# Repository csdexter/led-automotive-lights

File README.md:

#LED replacements for automotive light fixtures#

(C) 2013 Radu - Eosif Mihailescu <radu.mihailescu@linux360.ro>

All files in this repository are licensed under the
**GNU Generic Public License v3**, a copy of whose text can be accessed
 [here](http://www.gnu.org/licenses/gpl.html).

This repository contains [EDA](http://en.wikipedia.org/wiki/Electronic_design_automation) source files and associated software sources/configuration data for various LED-based replacements for common automotive light fixtures. The EDA files are in CadSoft Eagle 6 format. Only the `.SCH` (schematic) and `.BRD` (board) files are provided as all data needed for manufacturing can easily be derived from the former. No guarantee is made as to which minor version of Eagle was used to save the file, but it *may* be the latest at the time of this writing.

The board description files *may* contain routing information or be supplied unrouted. In the former case, the routing artwork *may* have been generated by either Eagle's internal autorouter or [FreeRouting](http://www.freerouting.net/).

All files included here are compatible with the free version of Eagle (i.e. describe PCBs having no more than 2 layers and measuring no more than 10cm by 8cm each).

Git tags will be used to mark specific revisions that were actually manufactured so that a correspondence between the evolution of the sources and the status of physical by-products can be maintained.

##WARNING##
*Unless and until explictily noted otherwise, the engineering materials here are laboratory quality and neither intended for manufacturing in production quantities nor for distribution (e.g. as kits) to end-users. The design data here does not explicitly follow any widely-accepted safety/security/EMI regulation or standard, therefore any manufacturing and/or usage in connection with live equipment is entirely at your own risk. Furthermore, the products described by the engineering materials here have not been subjected to any kind of type approval, including for use on a motor vehicle operating on public roads.*

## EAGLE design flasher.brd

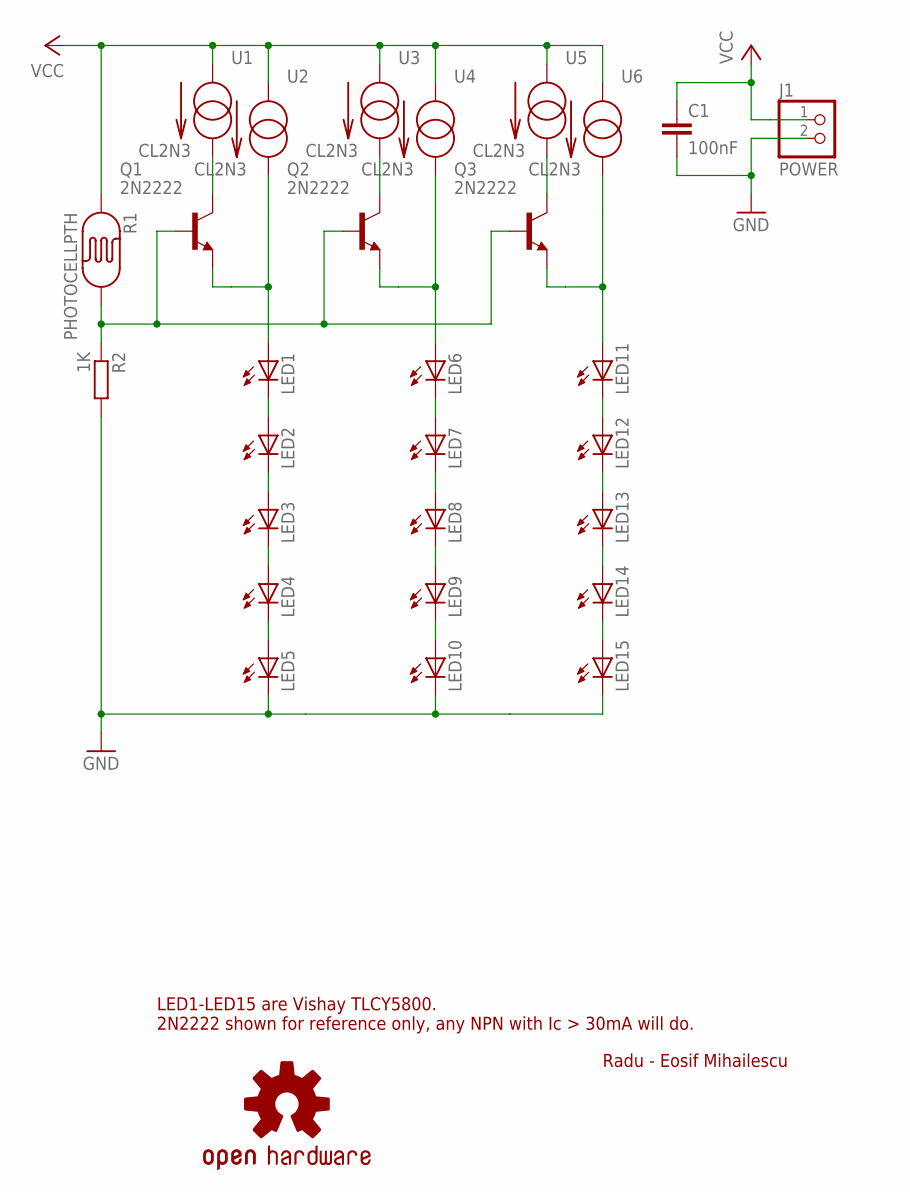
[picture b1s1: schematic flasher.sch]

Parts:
C1: 100nF; C050-025X075
J1: POWER; 1X02/90
LED1, LED2, LED3, LED4, LED5, LED6, LED7, LED8, LED9, LED10, LED11, LED12, LED13, LED14, LED15: LED5MM
LOGO1: OSHW-LOGOL; OSHW-LOGO-L
Q1, Q2, Q3: 2N2222; TO92-EBC
R1: PHOTOCELLPTH; PHOTOCELL
R2: 1K; 0204/7
U1, U2, U3, U4, U5, U6: CL2N3; TO-92

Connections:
GND: C1.2, J1.2, LED5.K (C), LED10.K (C), LED15.K (C), R2.2
unnamed: LED1.K (C), LED2.A
unnamed: LED2.K (C), LED3.A
unnamed: LED3.K (C), LED4.A
unnamed: LED1.A, Q1.E, U2.3 (OUT)
unnamed: LED4.K (C), LED5.A
unnamed: Q1.C, U1.3 (OUT)
unnamed: Q2.C, U3.3 (OUT)
unnamed: LED6.K (C), LED7.A
unnamed: LED7.K (C), LED8.A
unnamed: LED8.K (C), LED9.A
unnamed: LED6.A, Q2.E, U4.3 (OUT)
unnamed: LED9.K (C), LED10.A
unnamed: Q3.C, U5.3 (OUT)
unnamed: LED11.K (C), LED12.A
unnamed: LED12.K (C), LED13.A
unnamed: LED13.K (C), LED14.A
unnamed: LED11.A, Q3.E, U6.3 (OUT)
unnamed: LED14.K (C), LED15.A
SENSE: Q1.B, Q2.B, Q3.B, R1.2, R2.1
VCC: C1.1, J1.1, R1.1, U1.1 (IN), U2.1 (IN), U3.1 (IN), U4.1 (IN), U5.1 (IN), U6.1 (IN)

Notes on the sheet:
Radu - Eosif Mihailescu
LED1-LED15 are Vishay TLCY5800. 2N2222 shown for reference only, any NPN with Ic > 30mA will do.

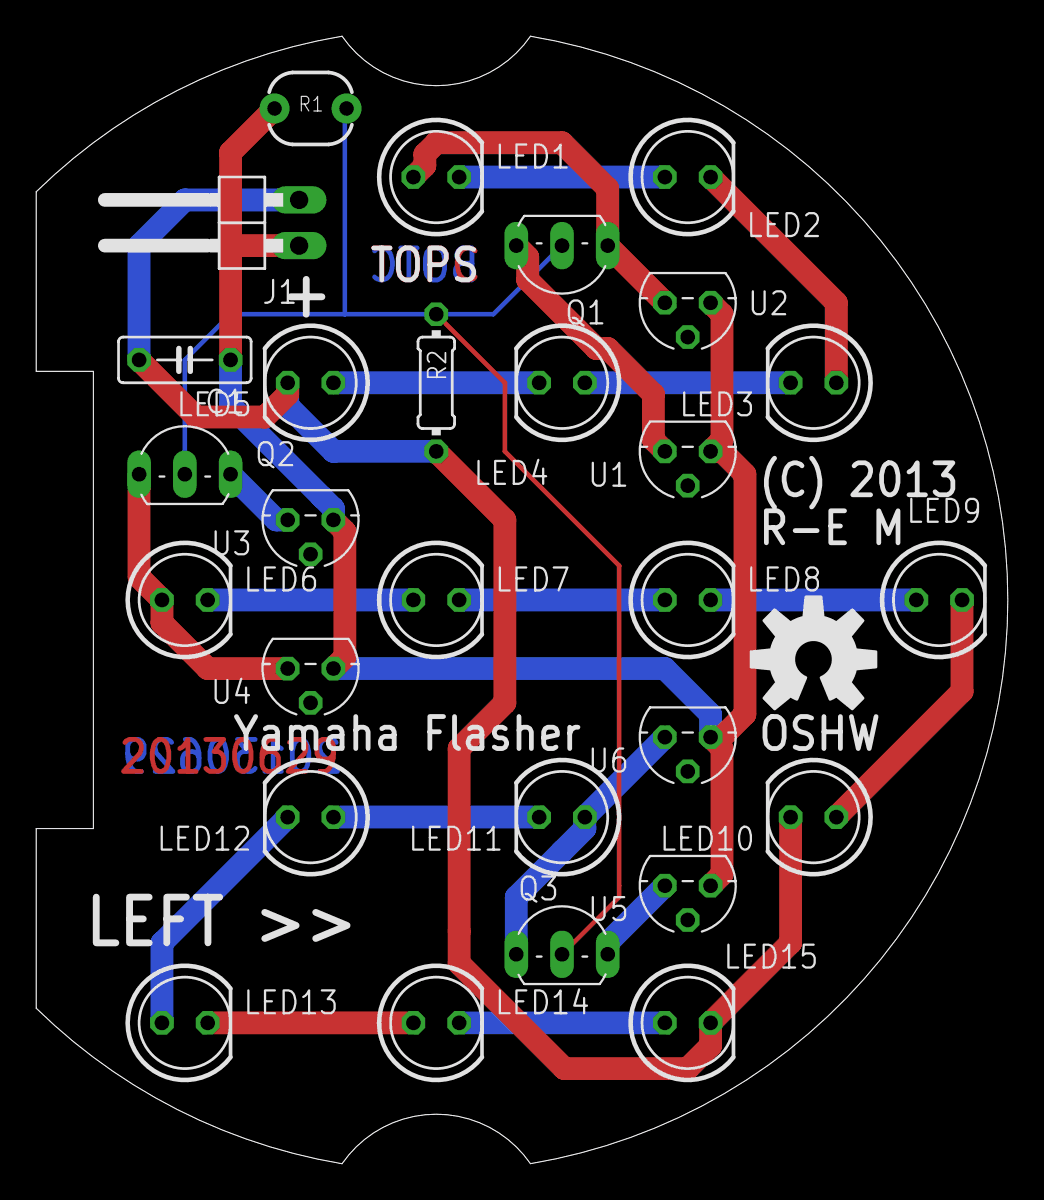
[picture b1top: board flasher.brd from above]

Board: 2 copper layers, 54.0 x 62.6 mm, 29 parts (0 on the bottom side), 21 nets.

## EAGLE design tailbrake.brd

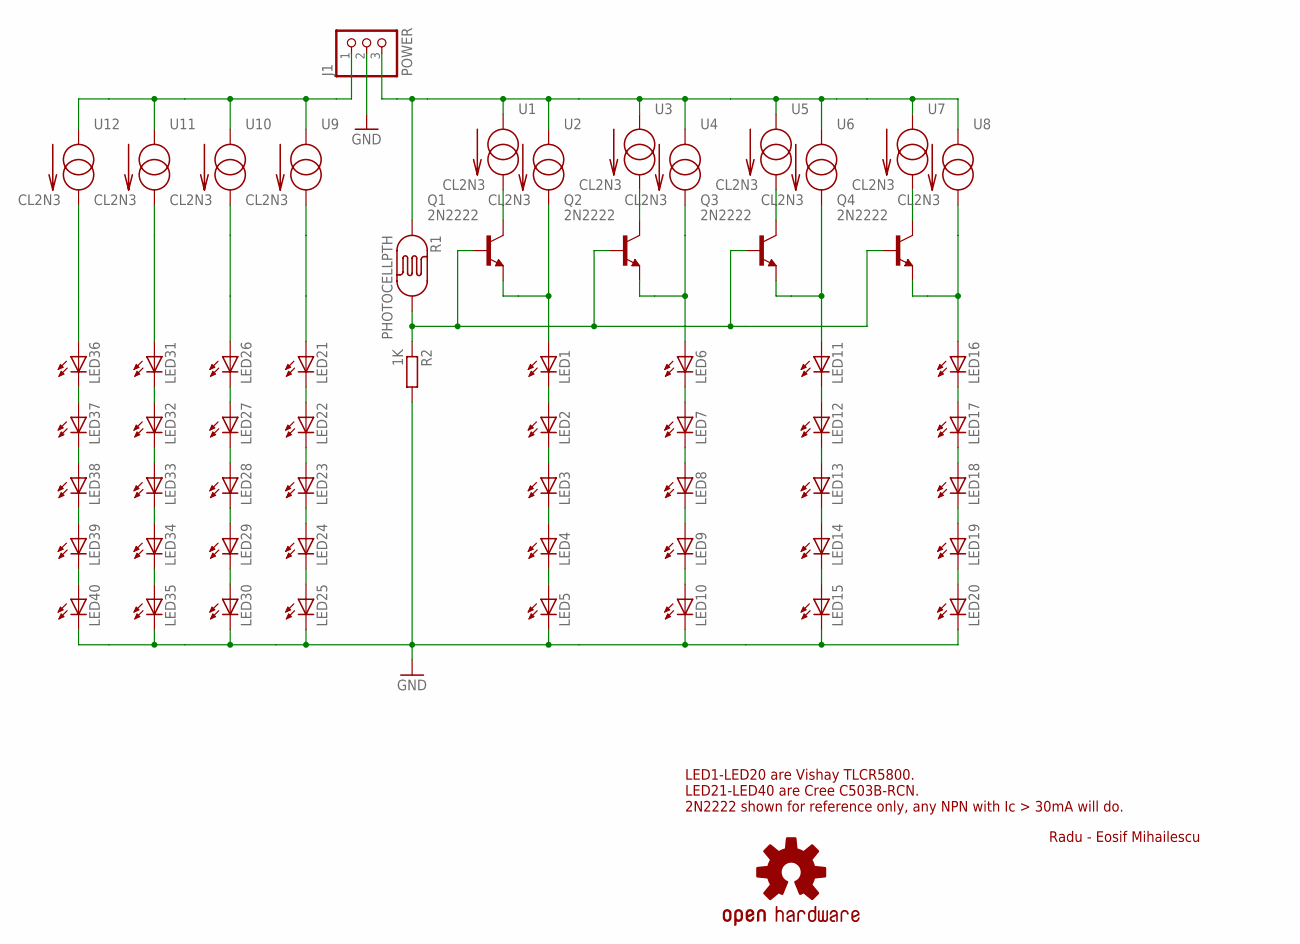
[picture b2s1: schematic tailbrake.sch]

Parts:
J1: POWER; 1X03/90
LED1, LED2, LED3, LED4, LED5, LED6, LED7, LED8, LED9, LED10, LED11, LED12, LED13, LED14, LED15, LED16, LED17, LED18, LED19, LED20, LED21, LED22, LED23, LED24, LED25, LED26, LED27, LED28, LED29, LED30, LED31, LED32, LED33, LED34, LED35, LED36, LED37, LED38, LED39, LED40: LED5MM
LOGO1: OSHW-LOGOL; OSHW-LOGO-L
Q1, Q2, Q3, Q4: 2N2222; TO92-EBC
R1: PHOTOCELLPTH; PHOTOCELL
R2: 1K; 0204/7
U1, U2, U3, U4, U5, U6, U7, U8, U9, U10, U11, U12: CL2N3; TO-92

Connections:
BRAKE: J1.3, R1.1, U1.1 (IN), U2.1 (IN), U3.1 (IN), U4.1 (IN), U5.1 (IN), U6.1 (IN), U7.1 (IN), U8.1 (IN)
GND: J1.2, LED5.K (C), LED10.K (C), LED15.K (C), LED20.K (C), LED25.K (C), LED30.K (C), LED35.K (C), LED40.K (C), R2.2
unnamed: LED1.K (C), LED2.A
unnamed: LED2.K (C), LED3.A
unnamed: LED3.K (C), LED4.A
unnamed: LED1.A, Q1.E, U2.3 (OUT)
unnamed: LED4.K (C), LED5.A
unnamed: Q1.C, U1.3 (OUT)
unnamed: Q2.C, U3.3 (OUT)
unnamed: LED6.K (C), LED7.A
unnamed: LED7.K (C), LED8.A
unnamed: LED8.K (C), LED9.A
unnamed: LED6.A, Q2.E, U4.3 (OUT)
unnamed: LED9.K (C), LED10.A
unnamed: Q3.C, U5.3 (OUT)
unnamed: LED11.K (C), LED12.A
unnamed: LED12.K (C), LED13.A
unnamed: LED13.K (C), LED14.A
unnamed: LED11.A, Q3.E, U6.3 (OUT)
unnamed: LED14.K (C), LED15.A
unnamed: LED16.K (C), LED17.A
unnamed: LED17.K (C), LED18.A
unnamed: LED18.K (C), LED19.A
unnamed: LED16.A, Q4.E, U8.3 (OUT)
unnamed: LED19.K (C), LED20.A
unnamed: Q4.C, U7.3 (OUT)
unnamed: LED21.K (C), LED22.A
unnamed: LED22.K (C), LED23.A
unnamed: LED23.K (C), LED24.A
unnamed: LED21.A, U9.3 (OUT)
unnamed: LED24.K (C), LED25.A
unnamed: LED26.K (C), LED27.A
unnamed: LED27.K (C), LED28.A
unnamed: LED28.K (C), LED29.A
unnamed: LED26.A, U10.3 (OUT)
unnamed: LED29.K (C), LED30.A
unnamed: LED31.K (C), LED32.A
unnamed: LED32.K (C), LED33.A
unnamed: LED33.K (C), LED34.A
unnamed: LED31.A, U11.3 (OUT)
unnamed: LED34.K (C), LED35.A
unnamed: LED36.K (C), LED37.A
unnamed: LED37.K (C), LED38.A
unnamed: LED38.K (C), LED39.A
unnamed: LED36.A, U12.3 (OUT)
unnamed: LED39.K (C), LED40.A
SENSE: Q1.B, Q2.B, Q3.B, Q4.B, R1.2, R2.1
TAIL: J1.1, U9.1 (IN), U10.1 (IN), U11.1 (IN), U12.1 (IN)

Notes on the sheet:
Radu - Eosif Mihailescu
LED1-LED20 are Vishay TLCR5800. LED21-LED40 are Cree C503B-RCN. 2N2222 shown for reference only, any NPN with Ic > 30mA will do.

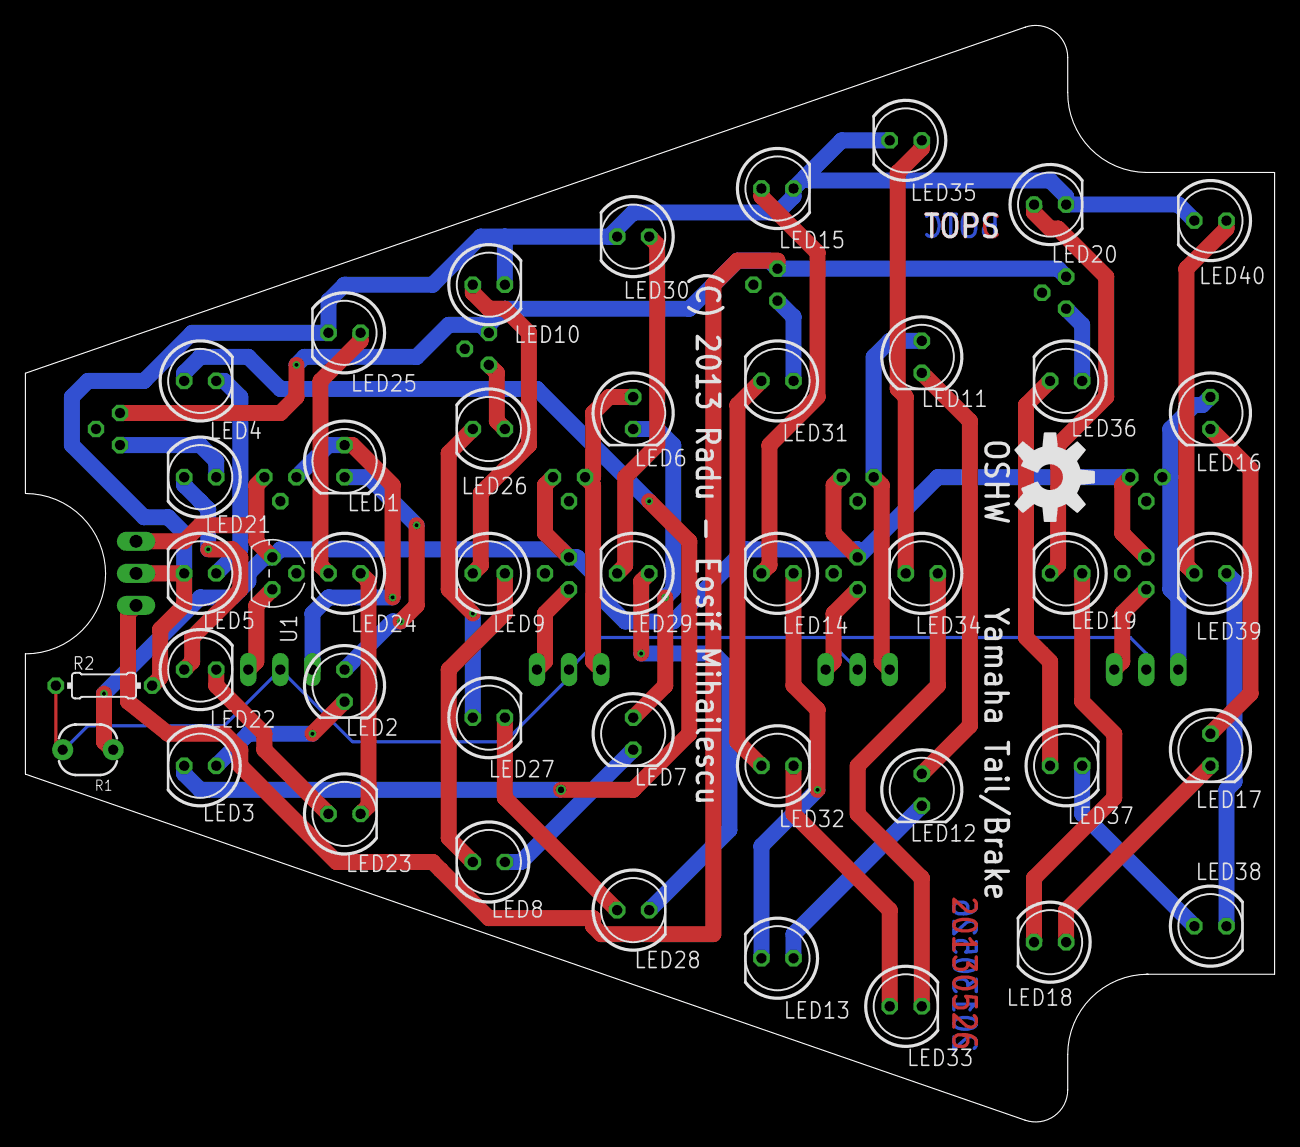
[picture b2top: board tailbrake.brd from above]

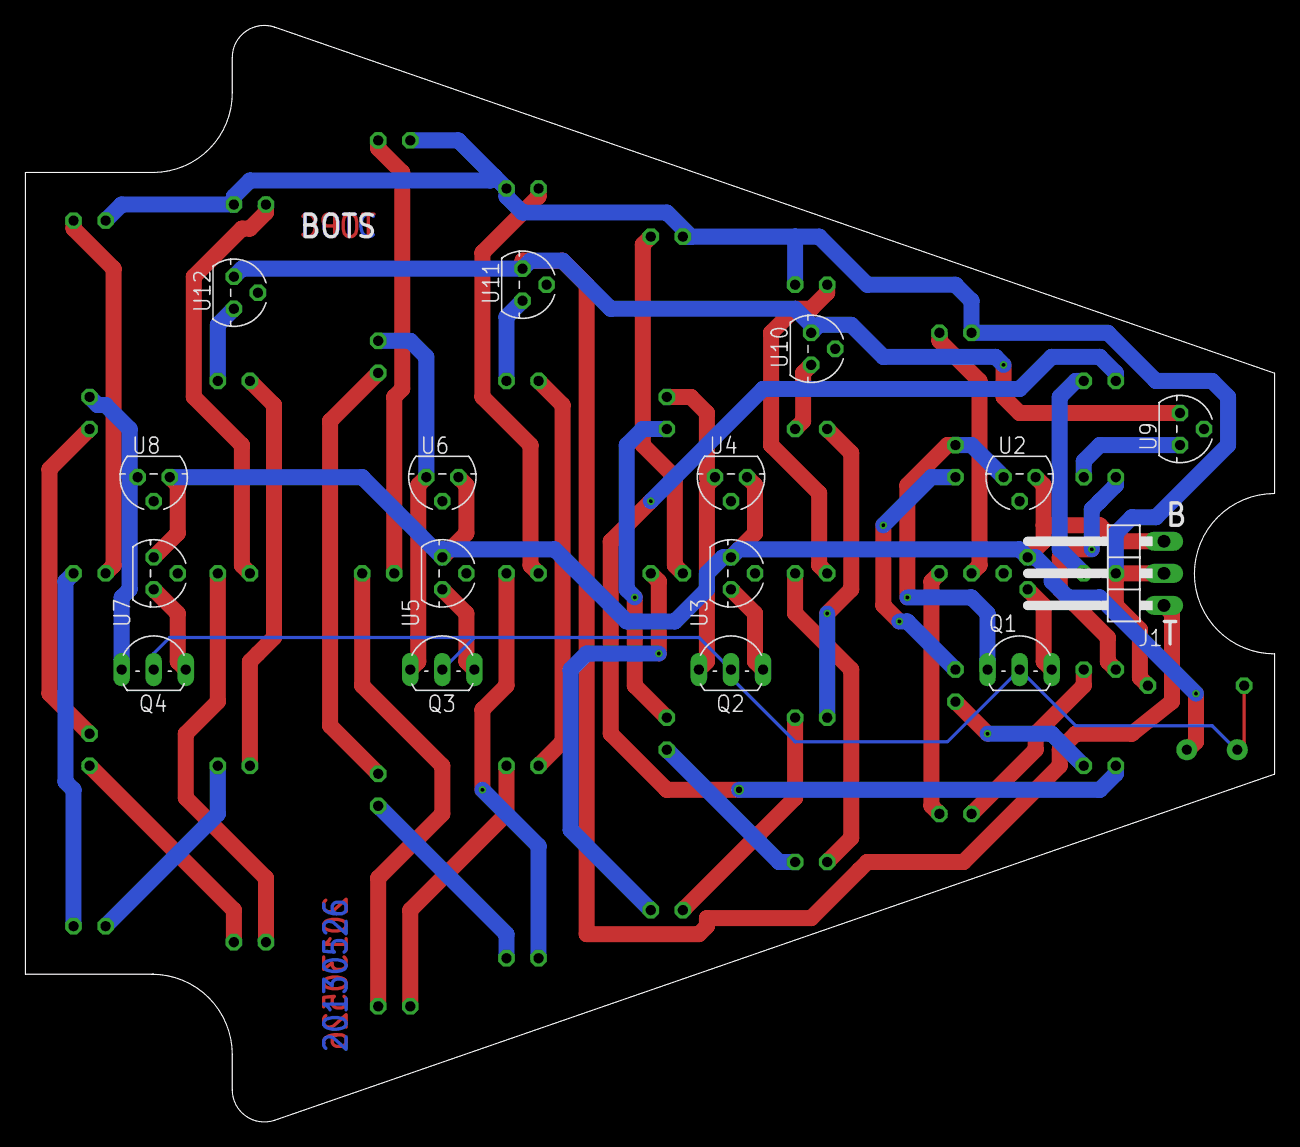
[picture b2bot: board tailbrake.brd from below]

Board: 2 copper layers, 98.9 x 86.8 mm, 60 parts (16 on the bottom side), 48 nets.

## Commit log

2013-05-22 Initial check-in: - flasher schematic and board for Yamaha cruiser -style flasher/indicator lights - three assembly versions: Simple, Dimmed (less light in darkness) and Pro (MCU-controlled)
2013-05-23 Final version, so far - brought flasher to ready for manufacture - done away with Pro assembly variant, not feasible - made design more robust, doing away with power resistor - sorted top silk, added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
2013-05-25 Added tail/brake light design: - 20 wide angle LEDs for tail light, 20 narrow angle LEDs for brake light - same dimmer logic as for the flasher - still some fanout to do - still needs constraining to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
2013-05-26 Final version, so far - brought tail/brake to ready for manufacture - two assembly versions: simple and dimmed - sorted top/bottom silk, added branding and extra artwork
2013-06-29 BUGFIX: - added 0.1uF as recommended by Supertex CL2N3 datasheet - rotated power connector to make it more accessible during assembly

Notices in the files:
parts and their libraries:
SparkFun-Sensors: Licensing: CC v3.0 Share-Alike You are welcome to use this library for commercial purposes.
